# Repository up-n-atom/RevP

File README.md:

# Rev. Probe

## What is RevP?
RevP is a [Black Magic](https://github.com/blackmagic-debug/blackmagic) Probe v2.1 clone updated to include USB-C and high-speed SWO tracing in a keyfob form factor.

## Hardware
### Enclosure
The [enclosure](/Hardware/Enclosure) is designed with [FreeCAD](https://www.freecadweb.org/).

### PCB
The [PCB](/Hardware/PCB) schematic and layout were made with [KiCad](https://www.kicad.org/). The layout replicates a hand-drawn style by utilizing the following plugins: [Teardrops](https://github.com/NilujePerchut/kicad_scripts/tree/master/teardrops) and [RF-Tools round tracks](https://github.com/easyw/RF-tools-KiCAD/tree/master/round_tracks).

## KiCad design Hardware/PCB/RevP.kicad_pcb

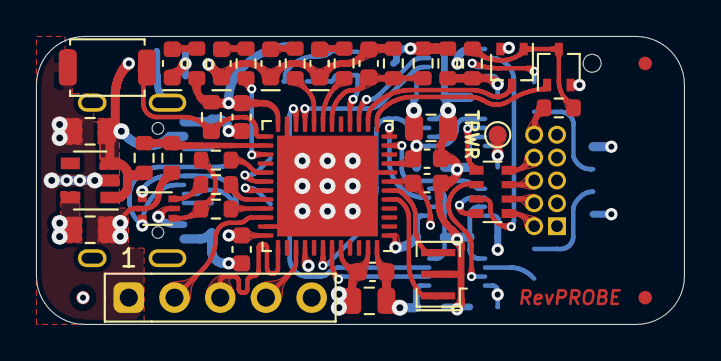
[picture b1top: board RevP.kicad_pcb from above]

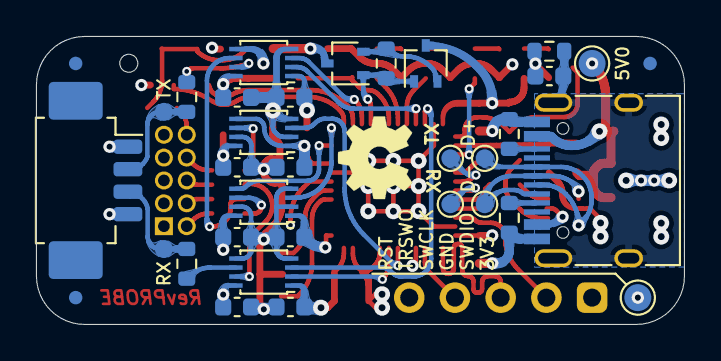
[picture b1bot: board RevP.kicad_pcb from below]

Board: 4 copper layers, 36.0 x 16.0 mm, 77 parts (34 on the bottom side), 58 nets.

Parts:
C1, C2, C3: C105; C_0805_2012Metric
C4, C6, C7, C8, C9: C104; C_0603_1608Metric
C5: C475; C_0805_2012Metric
C10, C11, C12, C13, C14, C15, C16, C17, C18, C19: C; C_0603_1608Metric
D1, D2, D3, D4: LED; LED_0603_1608Metric
FID1, FID2, FID3, FID4, FID5, FID6: Fiducial; Fiducial_0.75mm_Mask1.5mm
J1: Conn_01x05_Female; PinHeader_1x05_P2.54mm_Vertical
J2: Conn_01x04; Molex_PicoBlade_53261-0471_1x04-1MP_P1.25mm_Horizontal
J3: Conn_02x05_Odd_Even; PinHeader_2x05_P1.27mm_Vertical
J4: USB_C_Receptacle_USB2.0; USB_C_Receptacle_HRO_TYPE-C-31-M-12
Q1, Q2: DMG1012UW; SOT-323_SC-70
Q3, Q4: DMG1013UW; SOT-323_SC-70
R1, R2: 22E; R_0603_1608Metric
R3: 1K5; R_0603_1608Metric
R4, R15: 5K1; R_0603_1608Metric
R5, R6, R7, R8, R9, R10, R11, R12, R13, R14, R20, R21: R; R_0603_1608Metric
R16, R17, R18, R19: 100; R_0603_1608Metric
RN1: 100; R_Array_Convex_4x0603
RX: RX; TestPoint_Pad_D1.0mm
SW1: SW_Push; SW_Push_SPST_NO_Alps_SKRK
TP1: 3V3; TestPoint_Pad_D1.5mm
TP2: D-; TestPoint_Pad_D1.0mm
TP3: D+; TestPoint_Pad_D1.0mm
TP4: 5V; TestPoint_Pad_D1.5mm
TP5: TXD; TestPoint_Pad_D1.0mm
TP6: RXD; TestPoint_Pad_D1.0mm
TPWR: TPWR; TestPoint_Pad_D1.0mm
TX: TX; TestPoint_Pad_D1.0mm
U1: USBLC6-2P6; SOT-666
U2: STM32F103CBUx; QFN-48-1EP_7x7mm_P0.5mm_EP5.6x5.6mm
U3, U5, U7, U9: SN74LVC2T45DCUR; VSSOP-8_2.4x2.1mm_P0.5mm
U11: TLV73333PDBV; SOT-23-5
Y1: 8MHz; Resonator_SMD_muRata_CSTxExxV-3Pin_3.0x1.1mm

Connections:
+3V3: C2.1, C3.1, C4.1, C5.1, C6.1, C7.1, C8.1, C11.1, C13.1, C15.1, C17.1, Q3.3, R5.1, R9.1, TP1.1, U2.1, U2.9, U2.24, U2.36, U2.40, U2.48, U3.1, U3.5, U5.1, U5.5, U7.1, U9.1, U11.5
+5V: C1.1, J4.A4, J4.A9, J4.B4, J4.B9, R10.2, TP4.1, U1.5, U11.1, U11.3
/LED0: R6.1, U2.19
/LED1: R7.1, U2.20
/LED2: R8.2, U2.27
/PWR_BR: Q3.1, Q4.1, R20.1, U2.16
/RST: C9.1, J1.5, U2.7
/SHIELD: C19.2, J4.S1, R21.1
/SWCLK: J1.3, U2.37
/SWDIO: J1.2, U2.34
/TPWR: J2.1, J3.1, Q4.3, R13.1, R19.2
/TRACESWO: J1.4, U2.39
/USB_ATT: R2.2, R3.1, U1.4
/USB_P+: R2.1, U2.33
/USB_P-: R1.1, U2.32
/VBUS: R10.1, R11.2, U2.26
/iRST: Q2.1, U2.13
/iRST_SENSE: Q1.3, U2.14
/iRXD: U2.22, U7.3
/iTCK: U2.15, U5.3
/iTDI: U2.42, U3.3
/iTDO: U2.43, U7.2
/iTMS: U2.12, U9.3
/iTMS_DIR: U2.11, U9.5
/iTXD: U2.21, U5.2
/xRST: Q1.1, Q2.3, R12.2, R18.2
/xRXD: R17.2, U7.6
/xTCK: RN1.3, U5.6
/xTDI: RN1.1, U3.6
/xTDO: RN1.2, U7.7
/xTMS: RN1.4, U9.6
/xTPWR: C12.2, C14.2, C16.2, C18.2, R12.1, R19.1, TPWR.1, U3.8, U5.8, U7.8, U9.8
/xTXD: R16.1, U5.7
GND: C1.2, C2.2, C3.2, C4.2, C5.2, C6.2, C7.2, C8.2, C9.2, C10.2, C11.2, C12.1, C13.2, C14.1, C15.2, C16.1, C17.2, C18.1, C19.1, D1.1, D2.1, D3.1, D4.1, J1.1, J2.4, J3.3, J3.5, J3.9, J4.A1, J4.A12, J4.B1, J4.B12, Q1.2, Q2.2, R4.2, R11.1, R14.2, R15.1, R21.2, SW1.1, U1.2, U2.8, U2.23, U2.35, U2.44, U2.47, U2.49, U3.2, U3.4, U3.7, U5.4, U7.4, U7.5, U9.2, U9.4, U9.7, U11.2, Y1.2
unnamed: C10.1, R13.2, R14.1, U2.18
unnamed: D1.2, R6.2
unnamed: D2.2, R7.2
unnamed: D3.2, R8.1
unnamed: D4.2, R9.2
unnamed: J2.2, R16.2, TP5.1
unnamed: J2.3, R17.1, TP6.1
unnamed: J3.2, RN1.5
unnamed: J3.4, RN1.6
unnamed: J3.6, RN1.7
unnamed: J3.8, RN1.8
unnamed: J3.10, R18.1
unnamed: J4.A5, R4.1
unnamed: J4.A6, J4.B6, TP3.1, U1.3
unnamed: J4.A7, J4.B7, TP2.1, U1.1
unnamed: J4.B5, R15.2
unnamed: Q3.2, Q4.2, R20.2
unnamed: R1.2, U1.6
unnamed: R3.2, U2.29
unnamed: R5.2, SW1.2, U2.25
unnamed: TX.1, U2.30
unnamed: RX.1, U2.31
unnamed: U2.5, Y1.1
unnamed: U2.6, Y1.3

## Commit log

2023-04-24 Add RevP supported blackmagic firmware patch
2023-04-24 Add blackmagic as a module
2023-05-09 Update patch
    Add linker file
2023-05-09 Update blackmagic submodule
2023-05-19 Add Github action
    Add a build firmware github action
2023-05-19 Switch to GNU Arm Embdedded Toolchain
2023-05-19 Remove push action
2023-05-19 Update patch
2023-05-19 Upload build
2023-05-19 Fix artifact path in build action
